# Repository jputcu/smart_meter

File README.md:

Description
===========
Collect electricity and gas usage data from Belgian smart-meter into domoticz.

Links
=====
https://jensd.be/1205/linux/data-lezen-van-de-belgische-digitale-meter-met-de-p1-poort

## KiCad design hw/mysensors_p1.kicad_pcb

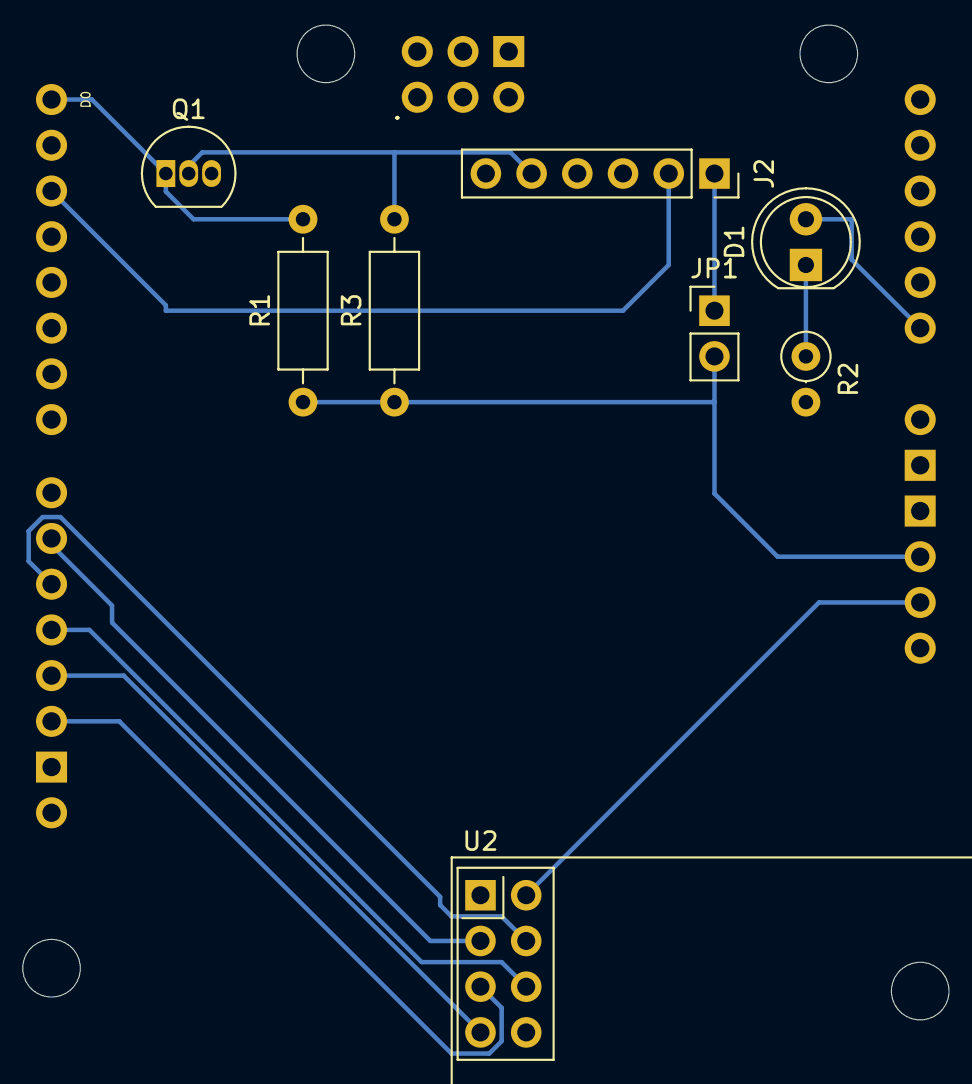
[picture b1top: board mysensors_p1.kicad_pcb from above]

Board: 2 copper layers, 9 parts (0 on the bottom side), 14 nets.

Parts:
A1: Arduino_Uno_R2_Shield
D1: LED; LED_D5.0mm
J2: Conn_01x06_Socket; PinSocket_1x06_P2.54mm_Vertical
JP1: DSMR +5V; PinHeader_1x02_P2.54mm_Vertical
Q1: BS170; TO-92_Inline
R1: 10k; R_Axial_DIN0207_L6.3mm_D2.5mm_P10.16mm_Horizontal
R2: 330; R_Axial_DIN0207_L6.3mm_D2.5mm_P2.54mm_Vertical
R3: 4k7; R_Axial_DIN0207_L6.3mm_D2.5mm_P10.16mm_Horizontal
U2: NRF24L01_Breakout; nRF24L01_Breakout

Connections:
+3V3: A1.3V3 (3.3V), U2.2 (VCC)
+5V: A1.5V1 (5V), JP1.2 (B), R1.1, R3.1
CE: A1.D9, U2.3 (CE)
CS: A1.D10 (D10_CS), U2.4 (~CSN)
DTR: A1.D2 (D2_INT0), J2.2
GND: A1.GND1 (GND), A1.GND2 (GND), A1.GND3 (GND), J2.3, J2.6, Q1.3 (S), R2.2, U2.1 (GND)
LED: A1.A0, D1.2 (A)
MISO: A1.D12, U2.7 (MISO)
MOSI: A1.D11, U2.6 (MOSI)
unnamed: D1.1 (K), R2.1
unnamed: J2.1, JP1.1 (A)
SCK: A1.D13, U2.5 (SCK)
TX: J2.5, Q1.2 (G), R3.2
TX inverted: A1.D0 (D0/RX), Q1.1 (D), R1.2

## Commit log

2022-11-13 Initial working POC
2022-11-13 Add basic README
2023-08-20 Add hardware design (Kicad)
2023-09-17 More or less working, just electricity power for now.
2023-09-17 Use own dsmr fork. Get rid of MySensors splash screen
2023-09-17 Extra ignores
2023-09-17 Force send every hour
2023-09-18 Update to latest dsmr library.
2023-09-22 Cleaner error LED handling.
2023-10-05 Error LED count represents parse error
